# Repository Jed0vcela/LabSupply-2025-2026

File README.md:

# Laboratorní napájecí zdroj + elektronická zátěž

Kombinovaný zdroj a elektronická zátěž na společných výstupních svorkách — vhodný pro nabíjení i vybíjení baterií.

## Napájení

- **USB-C** nebo **XT60** konektor (12–30 V, např. z akumulátorů)
- Výstupní napětí může být vyšší i nižší než vstupní (výstup **není galvanicky oddělen** od vstupu)

## Parametry

| Parametr | Hodnota |
|---|---|
| Výstupní napětí | 0 – 35 V |
| Výstupní proud (zdroj) | 0 – 4,5 A |
| Proudová zátěž | 0 – 3,8 A (max. 20 W) |

## Funkce

- **Zdroj** — nastavitelné napětí a proud (Vset, Iset)
- **Elektronická zátěž** — nastavitelný proudový sink (Isink), souběžně se zdrojem
- **Měřič kontinuity** — nastavitelný práh napětí, akustická signalizace
- **Ochrana výkonu** — konfigurovatelné limity Pout a Psink, ochrana při poklesu Vin
- **Kalibrace** — kalibrační průvodce (`Auto cal`) nebo ruční nastavení gain/offset, uložení do interní flash
- **Ukládání nastavení** — hodnoty Vset, Iset a Isink se ukládají do flash
- **IR dálkové ovládání** — NEC protokol, zatím není implementováno
- **LCD displej** — barevný 160×128 px, tři zobrazovací režimy

## Hardware

Raspberry Pi Pico (RP2040) · MCP4728 DAC · MCP23S17 · ST7735S LCD · rotační enkodér · NTC teplotní senzory · ventilátor · bzučák

## Dokumentace

| Dokument | Obsah |
|---|---|
| [Uživatelský manuál](N%C3%A1vody,%20postupy/uzivatelsky_manual.md) | ovládání, režimy, menu, ochrany |
| [Nahrání firmwaru](N%C3%A1vody,%20postupy/nahrani_firmwaru.md) | jak nahrát `.uf2`, vymazání flash |
| [Kalibrace](N%C3%A1vody,%20postupy/kalibrace.md) | kalibrační průvodce a ruční kalibrace |
| [Vývoj](N%C3%A1vody,%20postupy/vyvoj.md) | build, struktura kódu, vydání `.uf2` |

Hotové programy: [`Kompilované programy/`](Kompilované%20programy/)

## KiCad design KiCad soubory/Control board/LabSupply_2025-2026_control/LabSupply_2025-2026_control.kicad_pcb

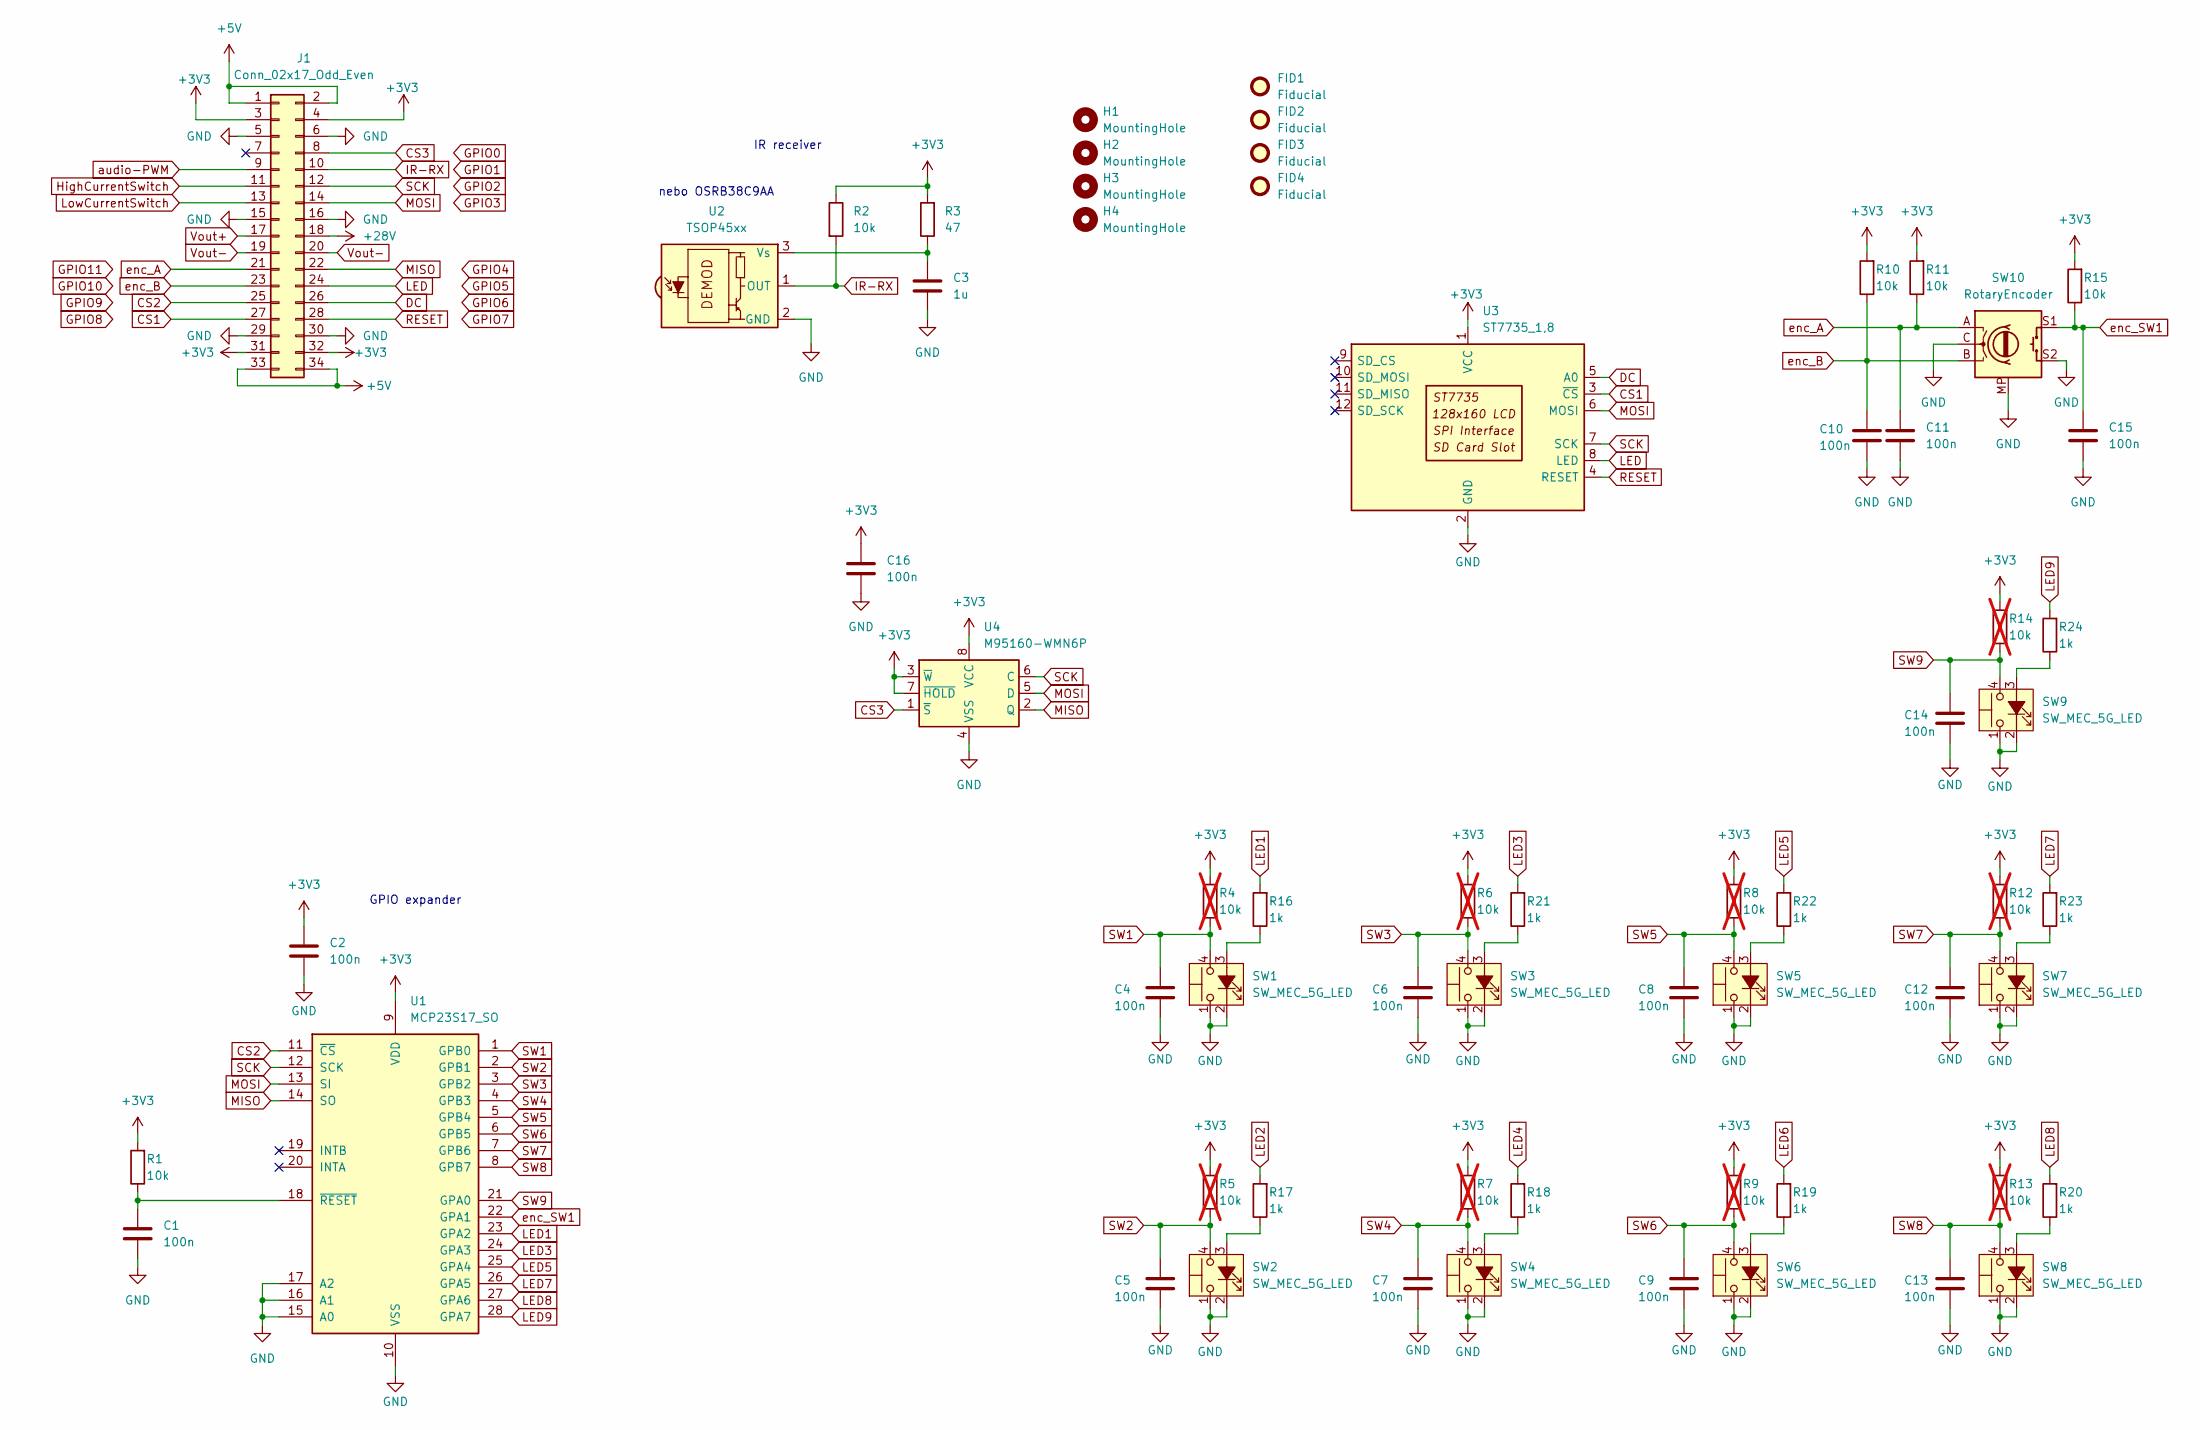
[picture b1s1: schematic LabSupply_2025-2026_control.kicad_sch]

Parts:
C1, C2, C4, C5, C6, C7, C8, C9, C10, C11, C12, C13, C14, C15, C16: 100n; C_0805_2012Metric_Pad1.18x1.45mm_HandSolder
C3: 1u; C_0805_2012Metric_Pad1.18x1.45mm_HandSolder
FID1, FID2, FID3, FID4: Fiducial; Fiducial_0.5mm_Mask1mm
H1, H2, H3, H4: MountingHole; MountingHole_2.5mm
J1: Conn_02x17_Odd_Even; IDC-Header_2x17_P2.54mm_Vertical
R1, R2, R10, R11, R15: 10k; R_0805_2012Metric_Pad1.20x1.40mm_HandSolder
R3: 47; R_0805_2012Metric_Pad1.20x1.40mm_HandSolder
R4, R5, R6, R7, R8, R9, R12, R13, R14: 10k; R_0805_2012Metric_Pad1.20x1.40mm_HandSolder; not fitted
R16, R17, R18, R19, R20, R21, R22, R23, R24: 1k; R_0805_2012Metric_Pad1.20x1.40mm_HandSolder
SW1, SW2, SW3, SW4, SW5, SW6, SW7, SW8, SW9: SW_MEC_5G_LED; SW_Cherry_MX_1.00u_PCB_LED
SW10: RotaryEncoder; RotaryEncoder_Alps_EC11E-Switch_Vertical_H20mm
U1: MCP23S17_SO; SOIC-28W_7.5x17.9mm_P1.27mm
U2: TSOP45xx; Vishay_MOLD-3Pin
U3: ST7735_1,8; ST7735_1,8_128x160
U4: M95160-WMN6P; SOIC-8_3.9x4.9mm_P1.27mm

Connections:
+3V3: C2.1, C16.1, J1.3, J1.4, J1.31, J1.32, R1.2, R2.1, R3.2, R4.2, R5.2, R6.2, R7.2, R8.2, R9.2, R10.2, R11.2, R12.2, R13.2, R14.2, R15.2, U1.9 (VDD), U3.1 (VCC), U4.3 (~W), U4.7 (~HOLD), U4.8 (VCC)
+5V: J1.1, J1.2, J1.33, J1.34
+28V: J1.18
CS1: J1.27, U3.3 (~CS)
CS2: J1.25, U1.11 (~CS)
CS3: J1.8, U4.1 (~S)
DC: J1.26, U3.5 (A0)
GND: C1.2, C2.2, C3.2, C4.2, C5.2, C6.2, C7.2, C8.2, C9.2, C10.2, C11.2, C12.2, C13.2, C14.2, C15.2, C16.2, J1.5, J1.6, J1.15, J1.16, J1.29, J1.30, SW1.1, SW1.2, SW2.1, SW2.2, SW3.1, SW3.2, SW4.1, SW4.2, SW5.1, SW5.2, SW6.1, SW6.2, SW7.1, SW7.2, SW8.1, SW8.2, SW9.1, SW9.2, SW10.C, SW10.MP, SW10.S2, U1.10 (VSS), U1.15 (A0), U1.16 (A1), U1.17 (A2), U2.2 (GND), U3.2 (GND), U4.4 (VSS)
HighCurrentSwitch: J1.11
IR-RX: J1.10, R2.2, U2.1 (OUT)
LED: J1.24, U3.8 (LED)
LED1: R16.2, U1.23 (GPA2)
LED2: R17.2
LED3: R21.2, U1.24 (GPA3)
LED4: R18.2
LED5: R22.2, U1.25 (GPA4)
LED6: R19.2
LED7: R23.2, U1.26 (GPA5)
LED8: R20.2, U1.27 (GPA6)
LED9: R24.2, U1.28 (GPA7)
LowCurrentSwitch: J1.13
MISO: J1.22, U1.14 (SO), U4.2 (Q)
MOSI: J1.14, U1.13 (SI), U3.6 (MOSI), U4.5 (D)
unnamed: R16.1, SW1.3 (K)
unnamed: R17.1, SW2.3 (K)
unnamed: R21.1, SW3.3 (K)
unnamed: R18.1, SW4.3 (K)
unnamed: R22.1, SW5.3 (K)
unnamed: R19.1, SW6.3 (K)
unnamed: R23.1, SW7.3 (K)
unnamed: R20.1, SW8.3 (K)
unnamed: R24.1, SW9.3 (K)
unnamed: C1.1, R1.1, U1.18 (~RESET)
unnamed: C3.1, R3.1, U2.3 (Vs)
RESET: J1.28, U3.4 (RESET)
SCK: J1.12, U1.12 (SCK), U3.7 (SCK), U4.6 (C)
SW1: C4.1, R4.1, SW1.4 (A), U1.1 (GPB0)
SW2: C5.1, R5.1, SW2.4 (A), U1.2 (GPB1)
SW3: C6.1, R6.1, SW3.4 (A), U1.3 (GPB2)
SW4: C7.1, R7.1, SW4.4 (A), U1.4 (GPB3)
SW5: C8.1, R8.1, SW5.4 (A), U1.5 (GPB4)
SW6: C9.1, R9.1, SW6.4 (A), U1.6 (GPB5)
SW7: C12.1, R12.1, SW7.4 (A), U1.7 (GPB6)
SW8: C13.1, R13.1, SW8.4 (A), U1.8 (GPB7)
SW9: C14.1, R14.1, SW9.4 (A), U1.21 (GPA0)
Vout+: J1.17
Vout-: J1.19, J1.20
audio-PWM: J1.9
enc_A: C11.1, J1.21, R11.1, SW10.A
enc_B: C10.1, J1.23, R10.1, SW10.B
enc_SW1: C15.1, R15.1, SW10.S1, U1.22 (GPA1)

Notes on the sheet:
IR receiver
nebo OSRB38C9AA
GPIO expander

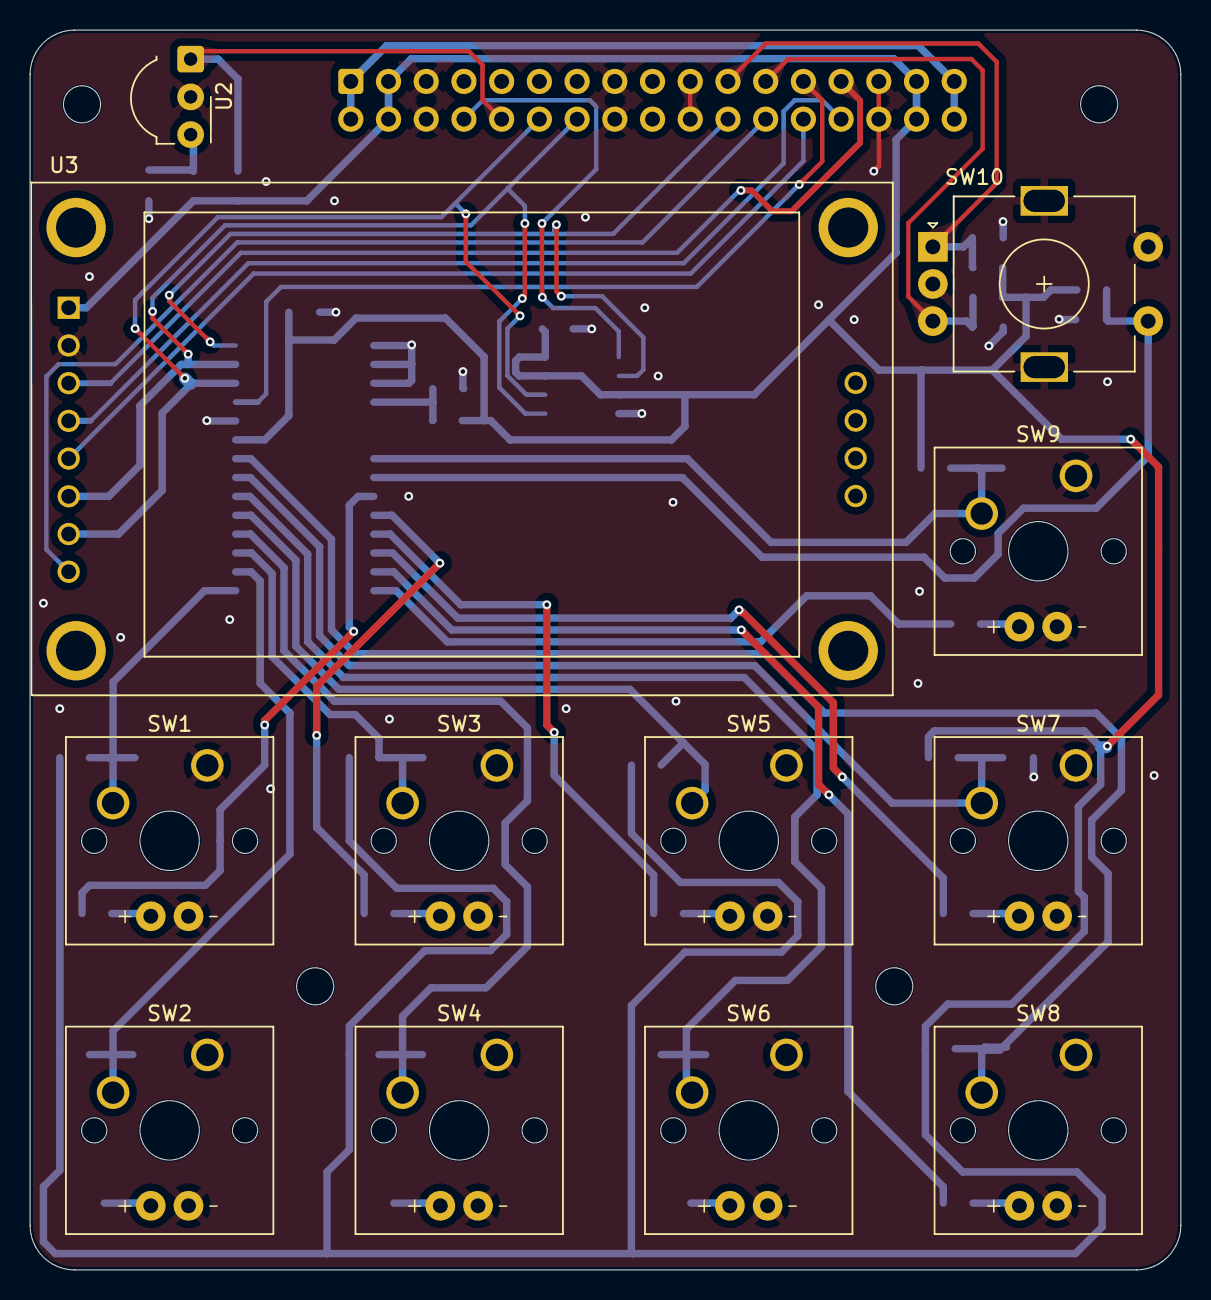
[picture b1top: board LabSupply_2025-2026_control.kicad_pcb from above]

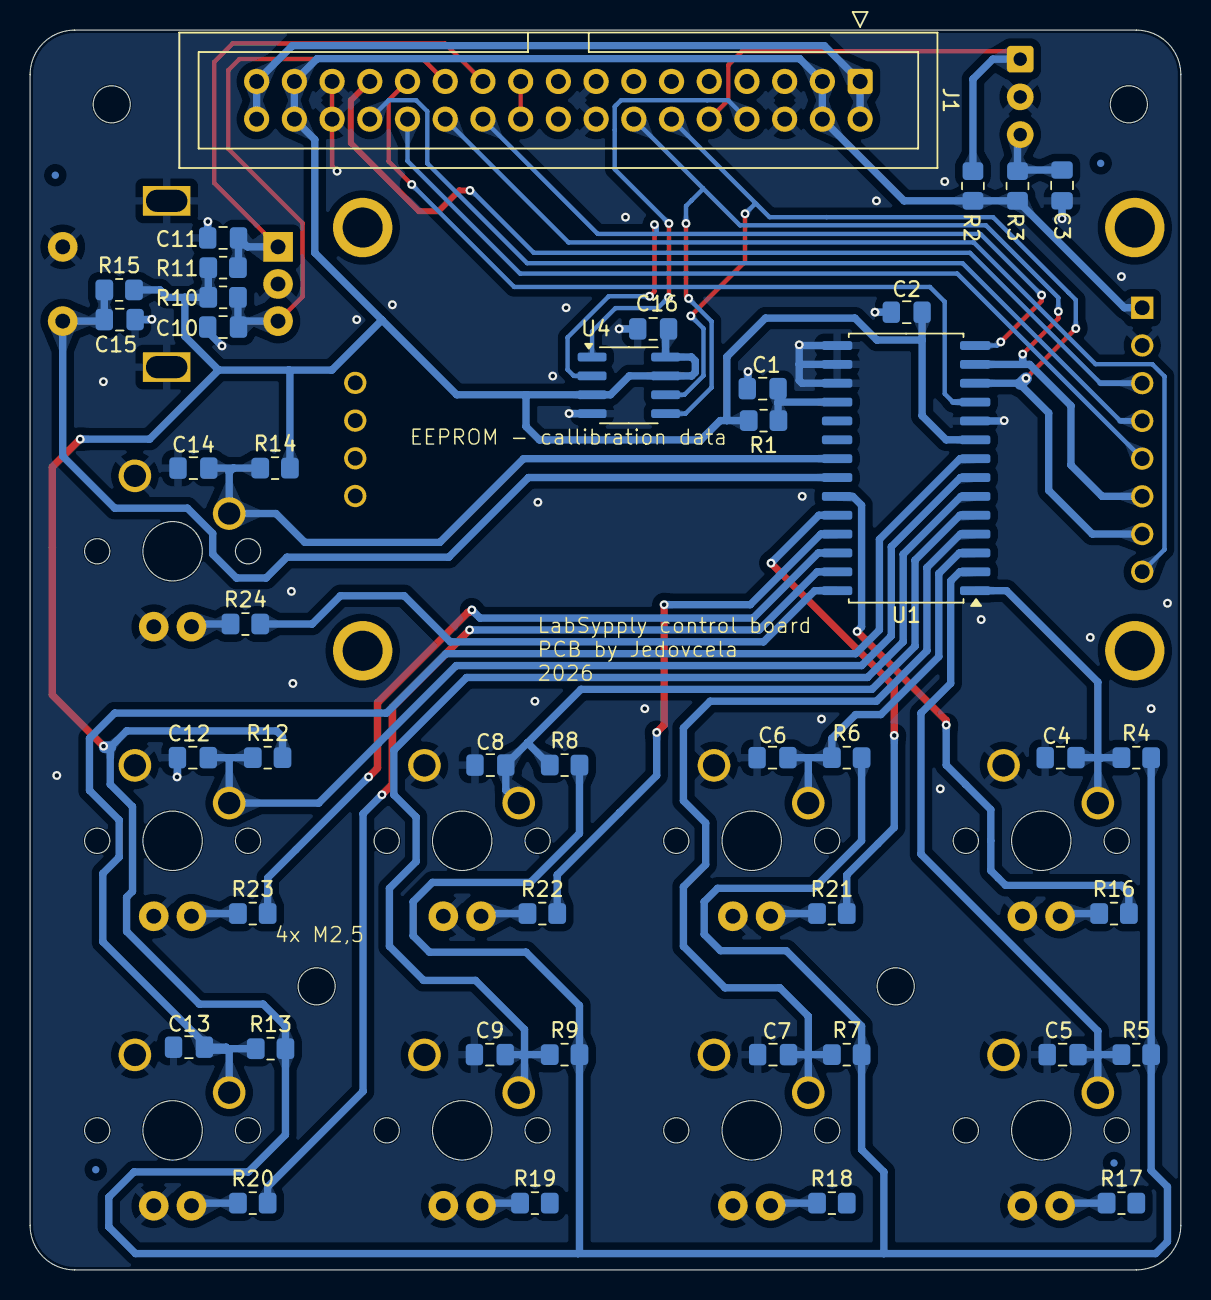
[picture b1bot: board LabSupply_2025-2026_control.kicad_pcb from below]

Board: 2 copper layers, 77.5 x 83.5 mm, 63 parts (47 on the bottom side), 43 nets.

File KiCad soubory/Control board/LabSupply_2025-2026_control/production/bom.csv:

Designator,Footprint,Quantity,Value,LCSC Part #
"C1, C10, C11, C12, C13, C14, C15, C16, C2, C4, C5, C6, C7, C8, C9",0805,15,100n,
C3,0805,1,1u,
J1,IDC-Header_2x17_P2.54mm_Vertical,1,Conn_02x17_Odd_Even,
"R1, R10, R11, R12, R13, R14, R15, R4, R5, R6, R7, R8, R9",0805,13,10k,
"R16, R17, R18, R19, R20, R21, R22, R23, R24",0805,9,1k,
R2,0805,1,22k,
R3,0805,1,47,
"SW1, SW2, SW3, SW4, SW5, SW6, SW7, SW8, SW9",SW_Cherry_MX_1.00u_PCB_LED,9,SW_MEC_5G_LED,
SW10,RotaryEncoder_Alps_EC11E-Switch_Vertical_H20mm,1,RotaryEncoder,
U1,SOIC-28W_7.5x17.9mm_P1.27mm,1,MCP23S17_SO,
U2,Vishay_MOLD-3Pin,1,TSOP45xx,
U3,"ST7735_1,8_128x160",1,"ST7735_1,8",
U4,SOIC-8_3.9x4.9mm_P1.27mm,1,M95160-WMN6P,

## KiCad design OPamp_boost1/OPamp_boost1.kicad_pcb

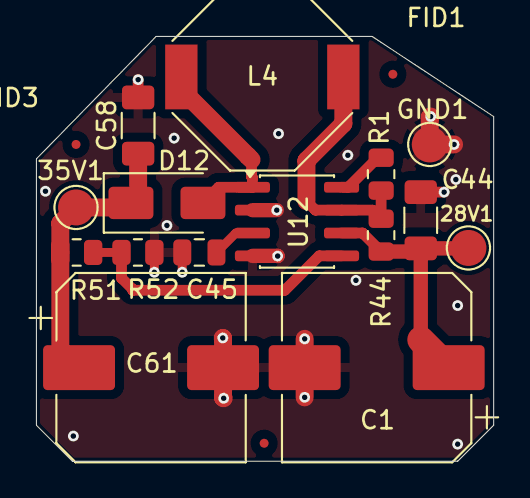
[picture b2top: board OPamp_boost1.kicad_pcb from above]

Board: 2 copper layers, 25.4 x 23.6 mm, 18 parts (0 on the bottom side), 8 nets.

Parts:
28V1, 35V1: TestPoint_Probe; TestPoint_Pad_D2.0mm
C1, C61: 220u 50V; CP_Elec_10x10
C44, C58: 1u; C_1206_3216Metric_Pad1.33x1.80mm_HandSolder
C45: 200p; C_0805_2012Metric
D12: D_Schottky; D_SMA
FID1, FID2, FID3: Fiducial; Fiducial_0.5mm_Mask1mm
GND1: TestPoint_Probe; TestPoint_Pad_D2.0mm
L4: 220u; L_Bourns-SRU1028_10.0x10.0mm
R1: 180; R_0805_2012Metric
R44: 1; R_0805_2012Metric
R51: 27k; R_0805_2012Metric
R52: 1k; R_0805_2012Metric
U12: MC34063AD; SOIC-8_3.9x4.9mm_P1.27mm

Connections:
+28V: 28V1.1, C1.1, C44.1, R44.2, U12.6 (Vin)
+36V: 35V1.1, C58.1, C61.1, D12.1 (K), R51.2
GND: C1.2, C44.2, C45.1, C58.2, C61.2, GND1.1, R52.1, U12.2 (SwE), U12.4 (GND)
unnamed: D12.2 (A), L4.2, U12.1 (SwC)
unnamed: R1.2, U12.8 (DC)
unnamed: L4.1, R1.1, R44.1, U12.7 (Ipk)
unnamed: C45.2, U12.3 (TC)
unnamed: R51.1, R52.2, U12.5 (Vfb)

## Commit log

2025-09-02 upload
2025-09-11 added buck power supplies
2025-10-03 almost complete schematics
2025-10-03 pdf upload
2025-11-06 upload power board V0.1
2026-05-11 initial upload
    3d files not yet finished.
    some errors in schematics
2026-05-16 bigger clearance on 2,2mm screws
2026-05-17 added chamfer
2026-05-17 upload
    needs to fit perfectly on cherrym MX buttons
2026-05-18 newer FW
    Fan control, beeper, menu + saving to flash, IR receiver, power calculation
2026-05-18 Create firmware3.uf2
    fixed freeze in callibration menu
2026-05-18 upload
    assembly almost finished.
    Added cheery MX buttons with text for multicolor 3D print
2026-05-18 upload buttons with bigger font
2026-05-19 bigger font
2026-05-19 Update button handle tapered hole V2 AMS.STL
    bigger font
2026-05-20 Update button handle tapered hole V2 AMS.STL
    0,1mm bigger text
2026-06-08 moved files around
2026-06-08 update
    now error mesaage shows on screen instead of only beeping.
    IR decoding now works with NEC protocol.
2026-06-08 Create flash_firmware.md
    Návod na nahrání novějšího FW
2026-06-08 Revise firmware flashing instructions
    Updated steps for flashing firmware on Raspberry Pi.
2026-06-08 fixed default constants
2026-06-08 Update IR remote control status in README
2026-06-08 Add images to firmware flashing instructions
2026-06-08 Add images to README documentation
    Added two images to the documentation section of the README.
2026-06-09 Clarify flash memory reset necessity in documentation
    Added note that flash memory reset is not usually needed.
